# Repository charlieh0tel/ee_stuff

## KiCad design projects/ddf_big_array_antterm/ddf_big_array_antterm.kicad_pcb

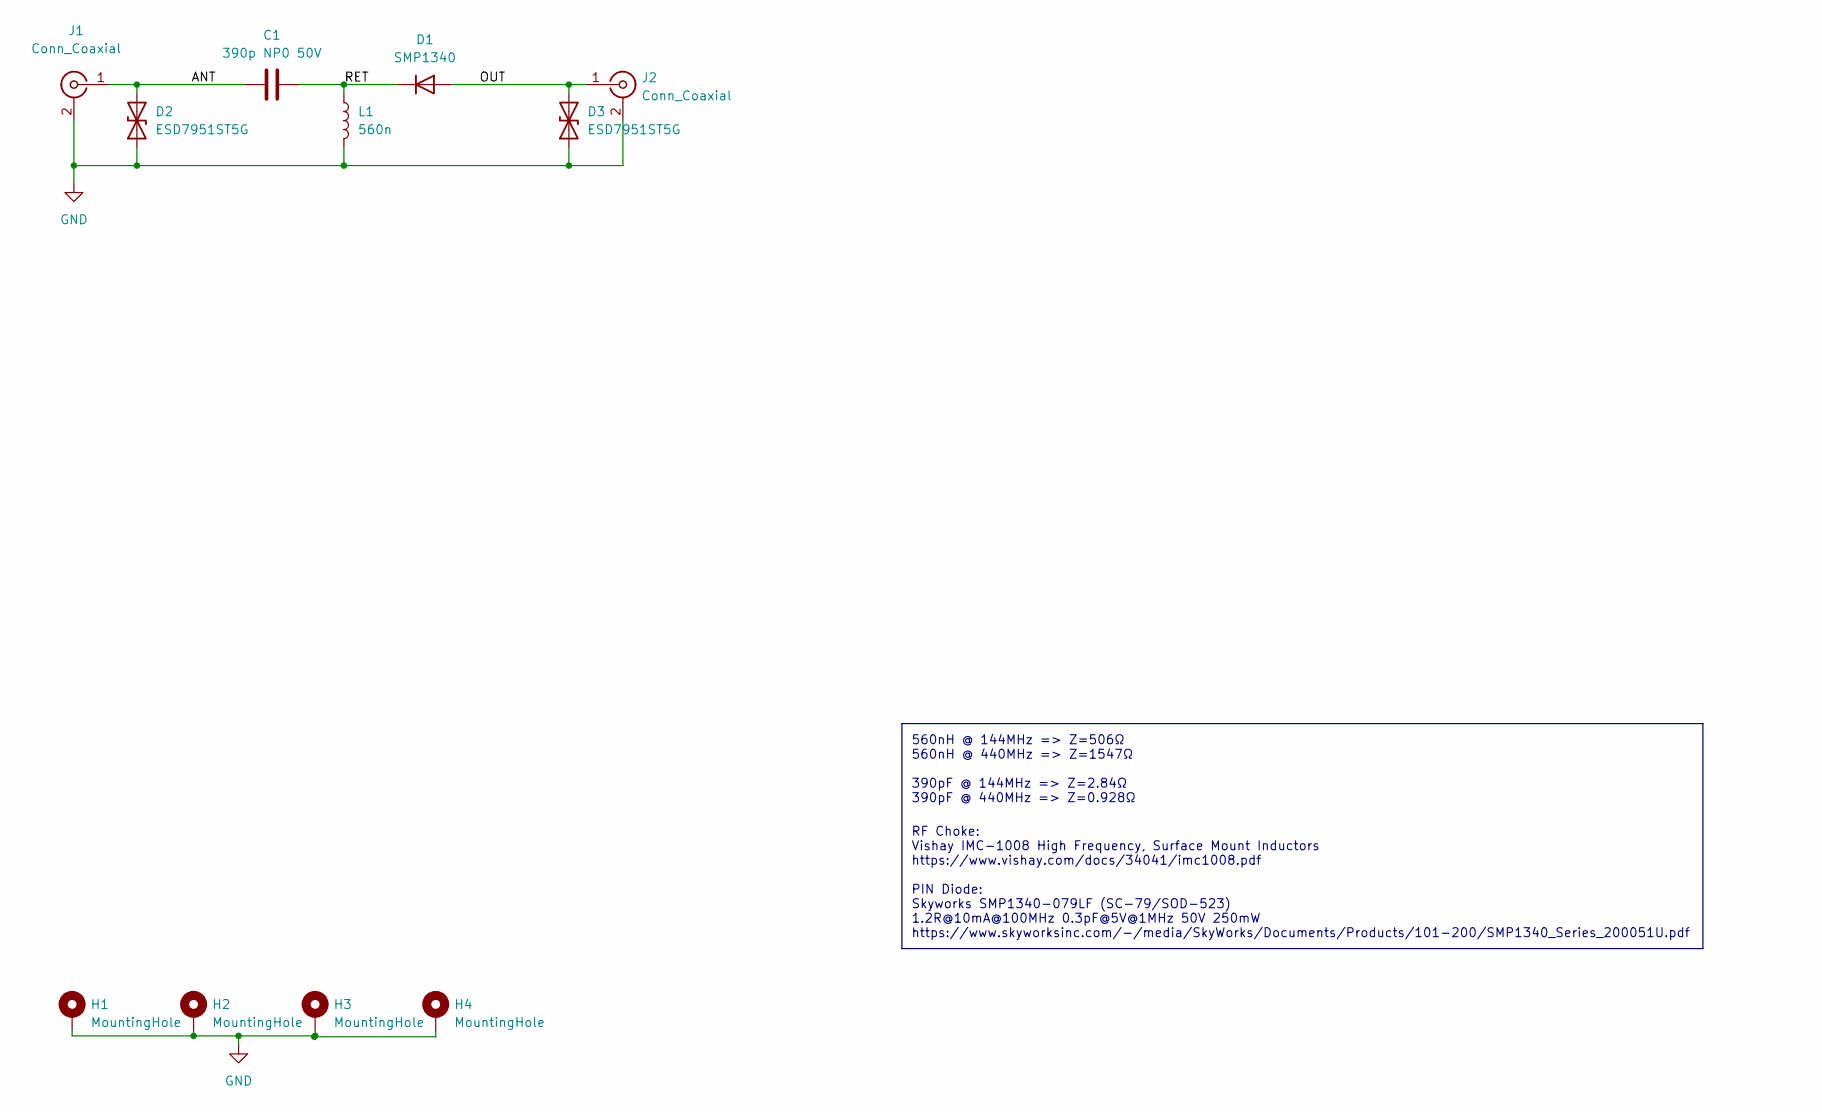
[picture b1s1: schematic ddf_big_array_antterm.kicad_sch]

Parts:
C1: 390p NP0 50V; C_0402_1005Metric; MPN GRM1555C1H391FA01D; LCSC C162100
D1: SMP1340; D_SOD-523; MPN SMP1340-079LF
D2, D3: ESD7951ST5G; D_SOD-923; MPN ESD7951ST5G
H1, H2, H3, H4: MountingHole; MountingHole_3.2mm_M3_Pad_TopBottom
J1: Conn_Coaxial; SMA_Molex-73391-0070_Vertical; LCSC C2874833
J2: Conn_Coaxial; SMA_Molex_73251-2200_Horizontal; LCSC C1509208
L1: 560n; IMC1008; MPN IMC1008ERR56J

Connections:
/ANT: C1.1, D2.2 (A2), J1.1 (In)
/OUT: D1.2 (A), D3.2 (A2), J2.1 (In)
/RET: C1.2, D1.1 (K), L1.1
GND: D2.1 (A1), D3.1 (A1), H1.1, H2.1, H3.1, H4.1, J1.2 (Ext), J2.2 (Ext), L1.2

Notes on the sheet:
RF Choke: Vishay IMC-1008 High Frequency, Surface Mount Inductors https://www.vishay.com/docs/34041/imc1008.pdf PIN Diode: Skyworks SMP1340-079LF (SC-79/SOD-523) 1.2R@10mA@100MHz 0.3pF@5V@1MHz 50V 250mW https://www.skyworksinc.com/-/media/SkyWorks/Documents/Products/101-200/SMP1340_Series_200051U.p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
560nH @ 144MHz => Z=506Ω 560nH @ 440MHz => Z=1547Ω 390pF @ 144MHz => Z=2.84Ω 390pF @ 440MHz => Z=0.928Ω

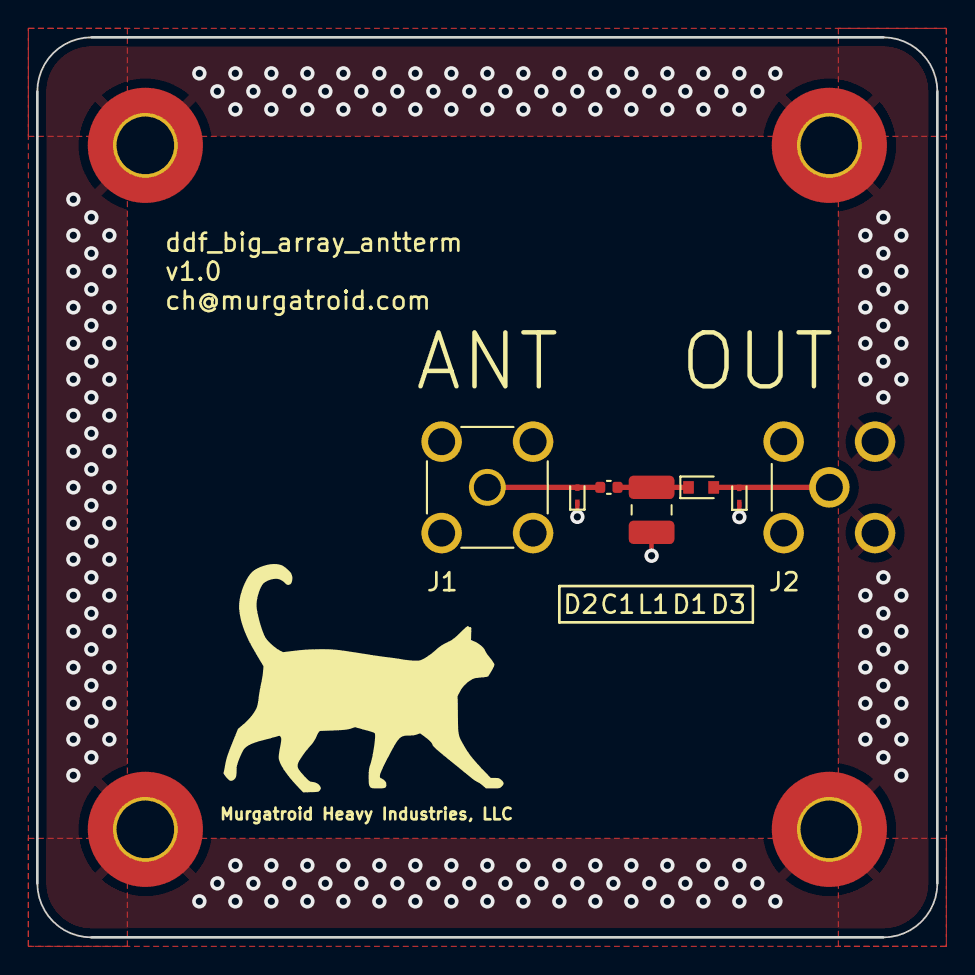
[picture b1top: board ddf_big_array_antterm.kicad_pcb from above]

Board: 4 copper layers, 50.0 x 50.0 mm, 11 parts (0 on the bottom side), 4 nets.

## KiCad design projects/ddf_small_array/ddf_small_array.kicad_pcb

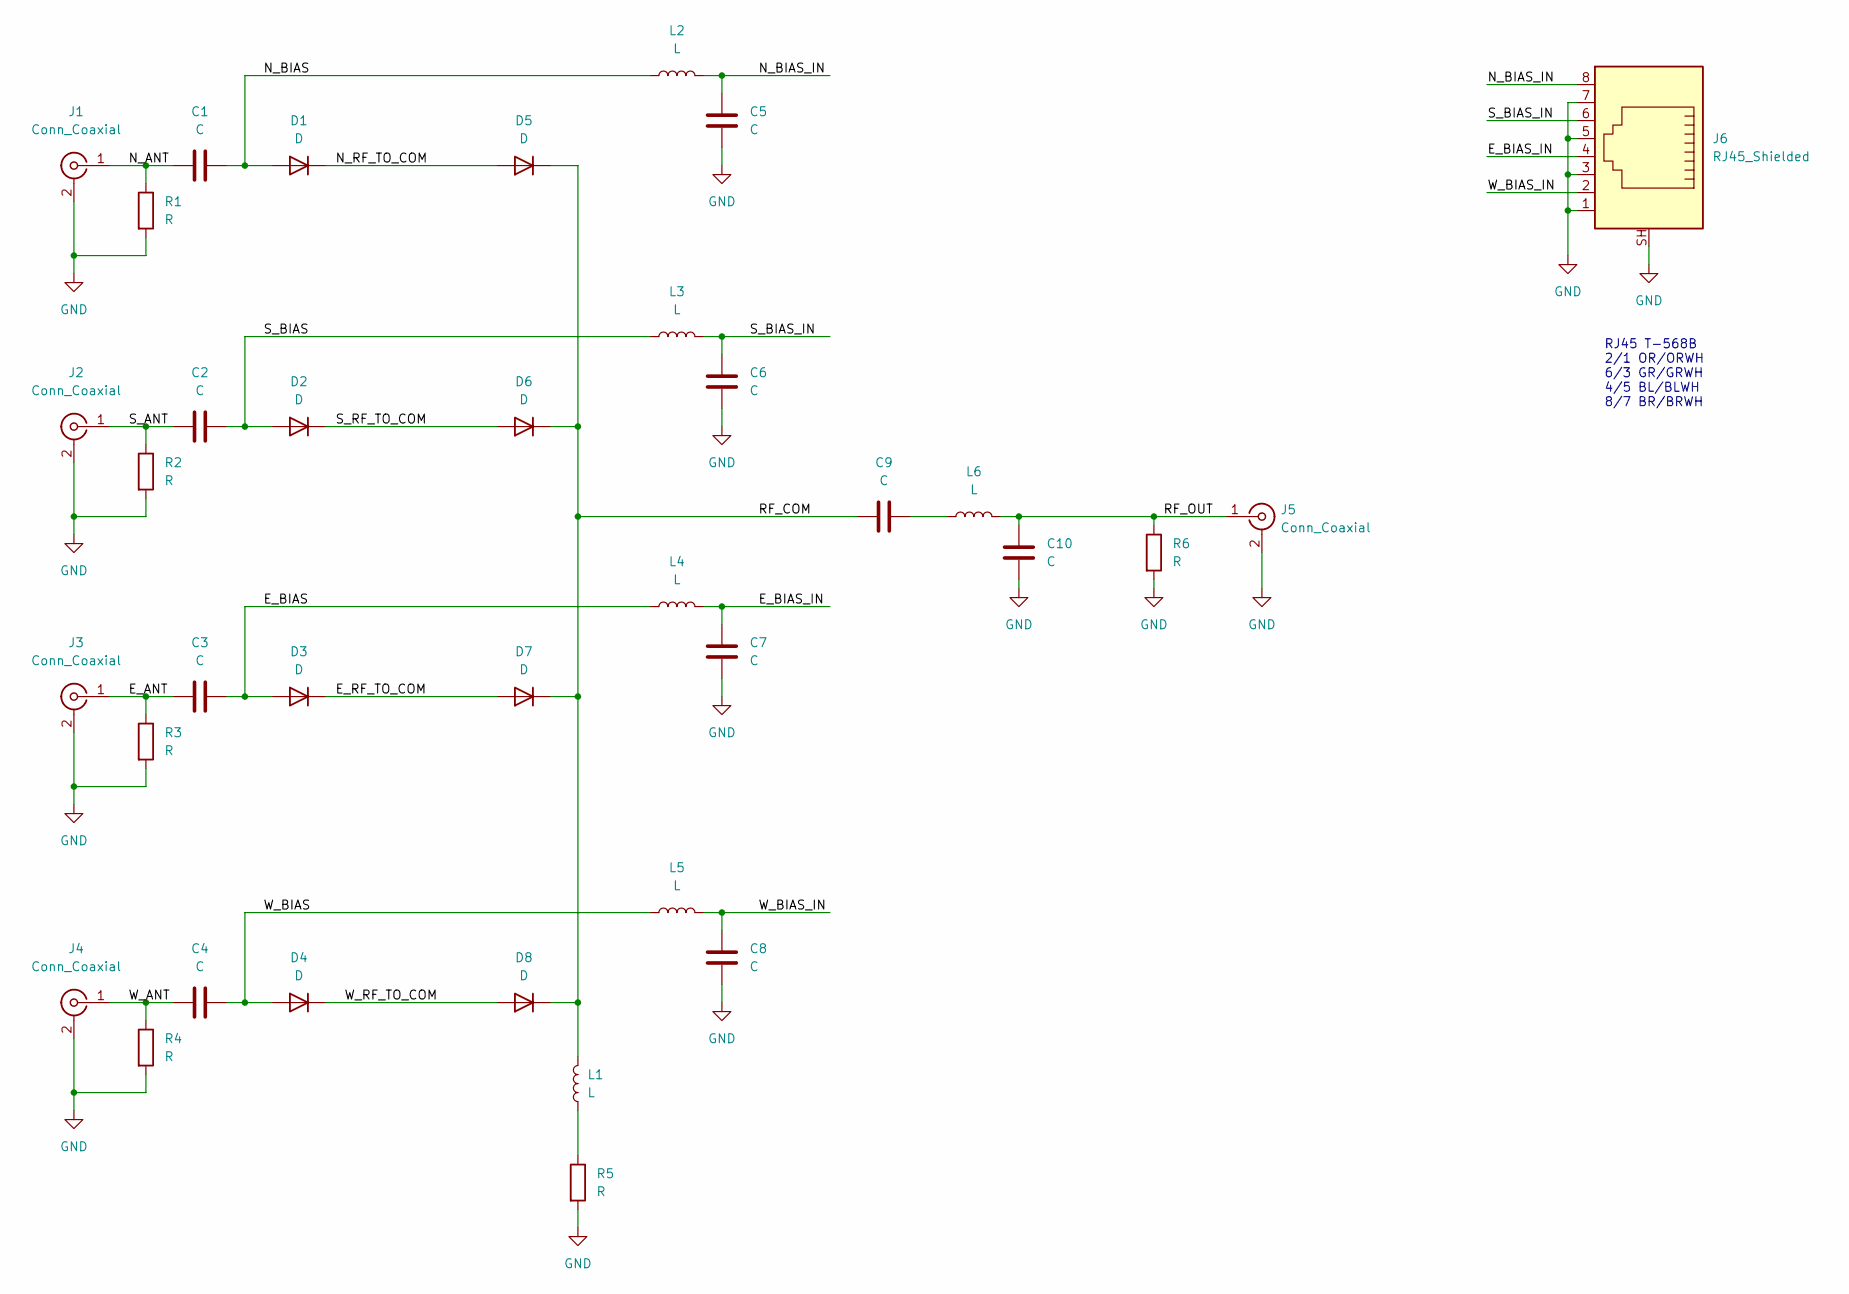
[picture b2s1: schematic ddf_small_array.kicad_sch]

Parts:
C1, C2, C3, C4, C5, C6, C7, C8, C9: C; C_0402_1005Metric
C10: C; C_0402_1005Metric_Pad0.74x0.62mm_HandSolder
D1, D2, D3, D4, D5, D6, D7, D8: D; D_SOD-323
J1, J2, J3, J4: Conn_Coaxial; SMA_Wurth_60312002114503_Vertical
J5: Conn_Coaxial; SMA_Molex_73251-2200_Horizontal
J6: RJ45_Shielded; RJ45_Wuerth_7499010001A_Horizontal
L1, L2, L3, L4, L5: L; L_0402_1005Metric
L6: L; L_0402_1005Metric_Pad0.77x0.64mm_HandSolder
R1, R2, R3, R4, R5, R6: R; R_0402_1005Metric

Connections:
/E_ANT: C3.2, J3.1 (In), R3.1
/E_BIAS: C3.1, D3.2 (A), L4.1
/E_BIAS_IN: C7.1, J6.4, L4.2
/E_RF_TO_COM: D3.1 (K), D7.2 (A)
/N_ANT: C1.2, J1.1 (In), R1.1
/N_BIAS: C1.1, D1.2 (A), L2.1
/N_BIAS_IN: C5.1, J6.8, L2.2
/N_RF_TO_COM: D1.1 (K), D5.2 (A)
/RF_COM: C9.1, D5.1 (K), D6.1 (K), D7.1 (K), D8.1 (K), L1.2
/RF_OUT: C10.1, J5.1 (In), L6.2, R6.1
/S_ANT: C2.2, J2.1 (In), R2.1
/S_BIAS: C2.1, D2.2 (A), L3.1
/S_BIAS_IN: C6.1, J6.6, L3.2
/S_RF_TO_COM: D2.1 (K), D6.2 (A)
/W_ANT: C4.2, J4.1 (In), R4.1
/W_BIAS: C4.1, D4.2 (A), L5.1
/W_BIAS_IN: C8.1, J6.2, L5.2
/W_RF_TO_COM: D4.1 (K), D8.2 (A)
GND: C5.2, C6.2, C7.2, C8.2, C10.2, J1.2 (Ext), J2.2 (Ext), J3.2 (Ext), J4.2 (Ext), J5.2 (Ext), J6.1, J6.3, J6.5, J6.7, J6.SH, R1.2, R2.2, R3.2, R4.2, R5.2, R6.2
unnamed: C9.2, L6.1
unnamed: L1.1, R5.1

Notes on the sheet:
RJ45 T-568B 2/1 OR/ORWH 6/3 GR/GRWH 4/5 BL/BLWH 8/7 BR/BRWH

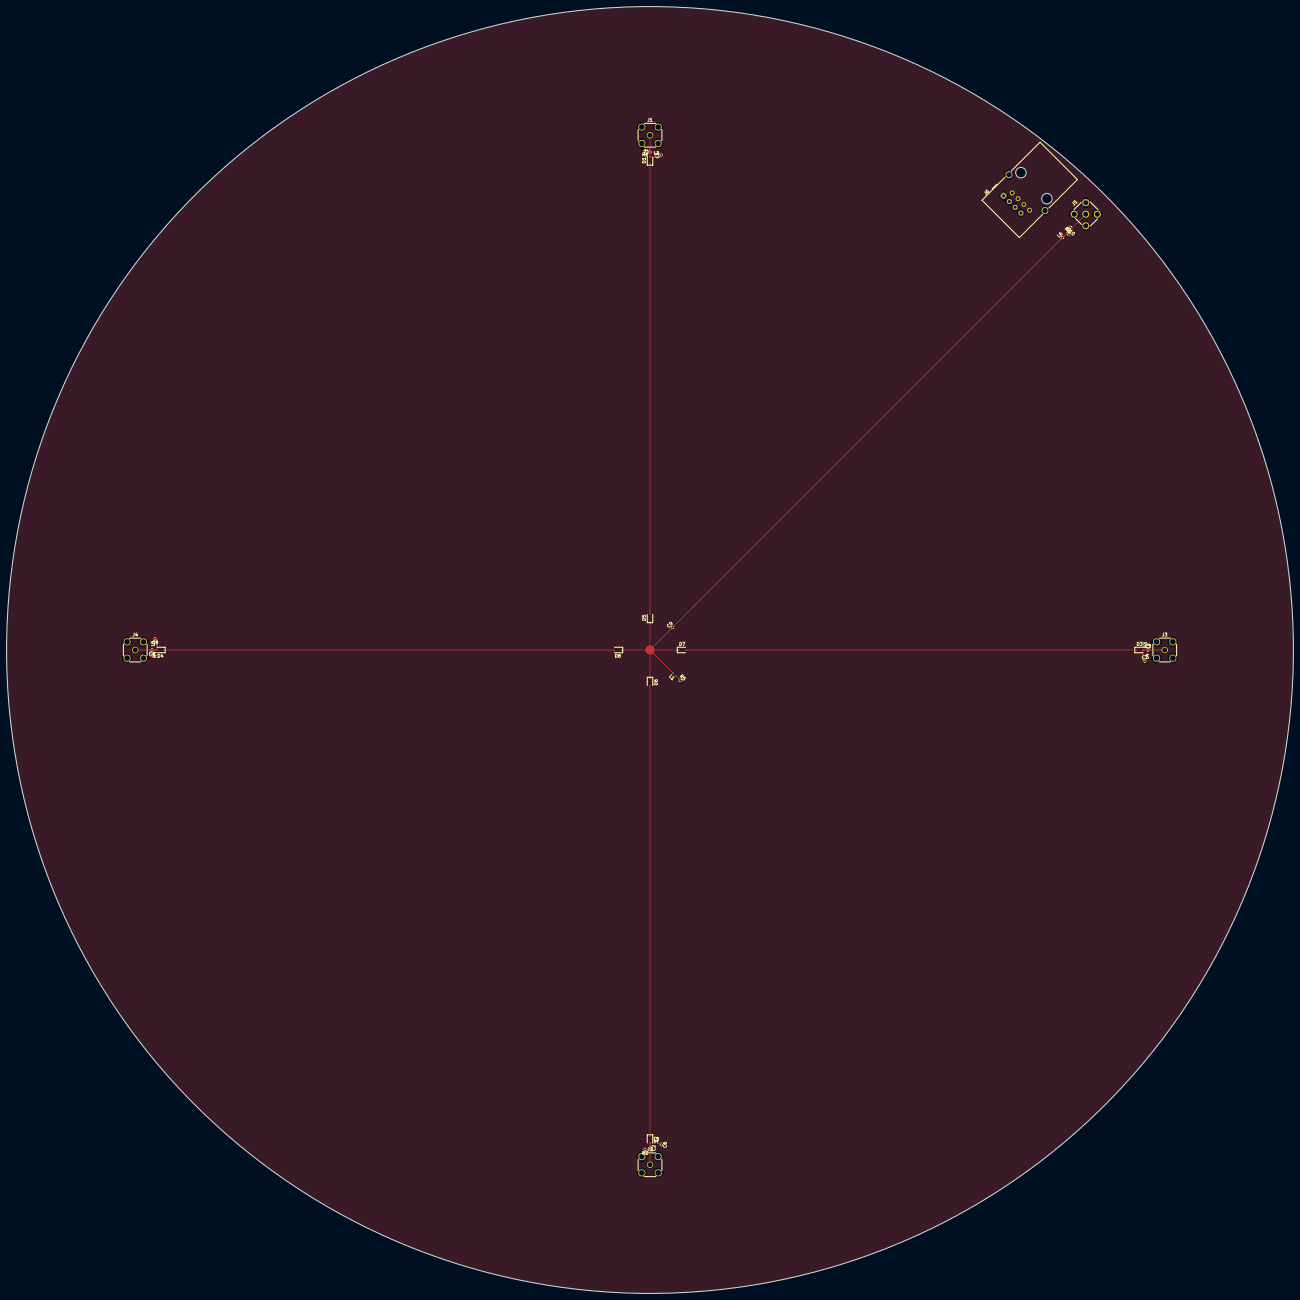
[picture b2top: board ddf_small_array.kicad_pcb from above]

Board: 2 copper layers, 400.0 x 400.0 mm, 36 parts (0 on the bottom side), 21 nets.

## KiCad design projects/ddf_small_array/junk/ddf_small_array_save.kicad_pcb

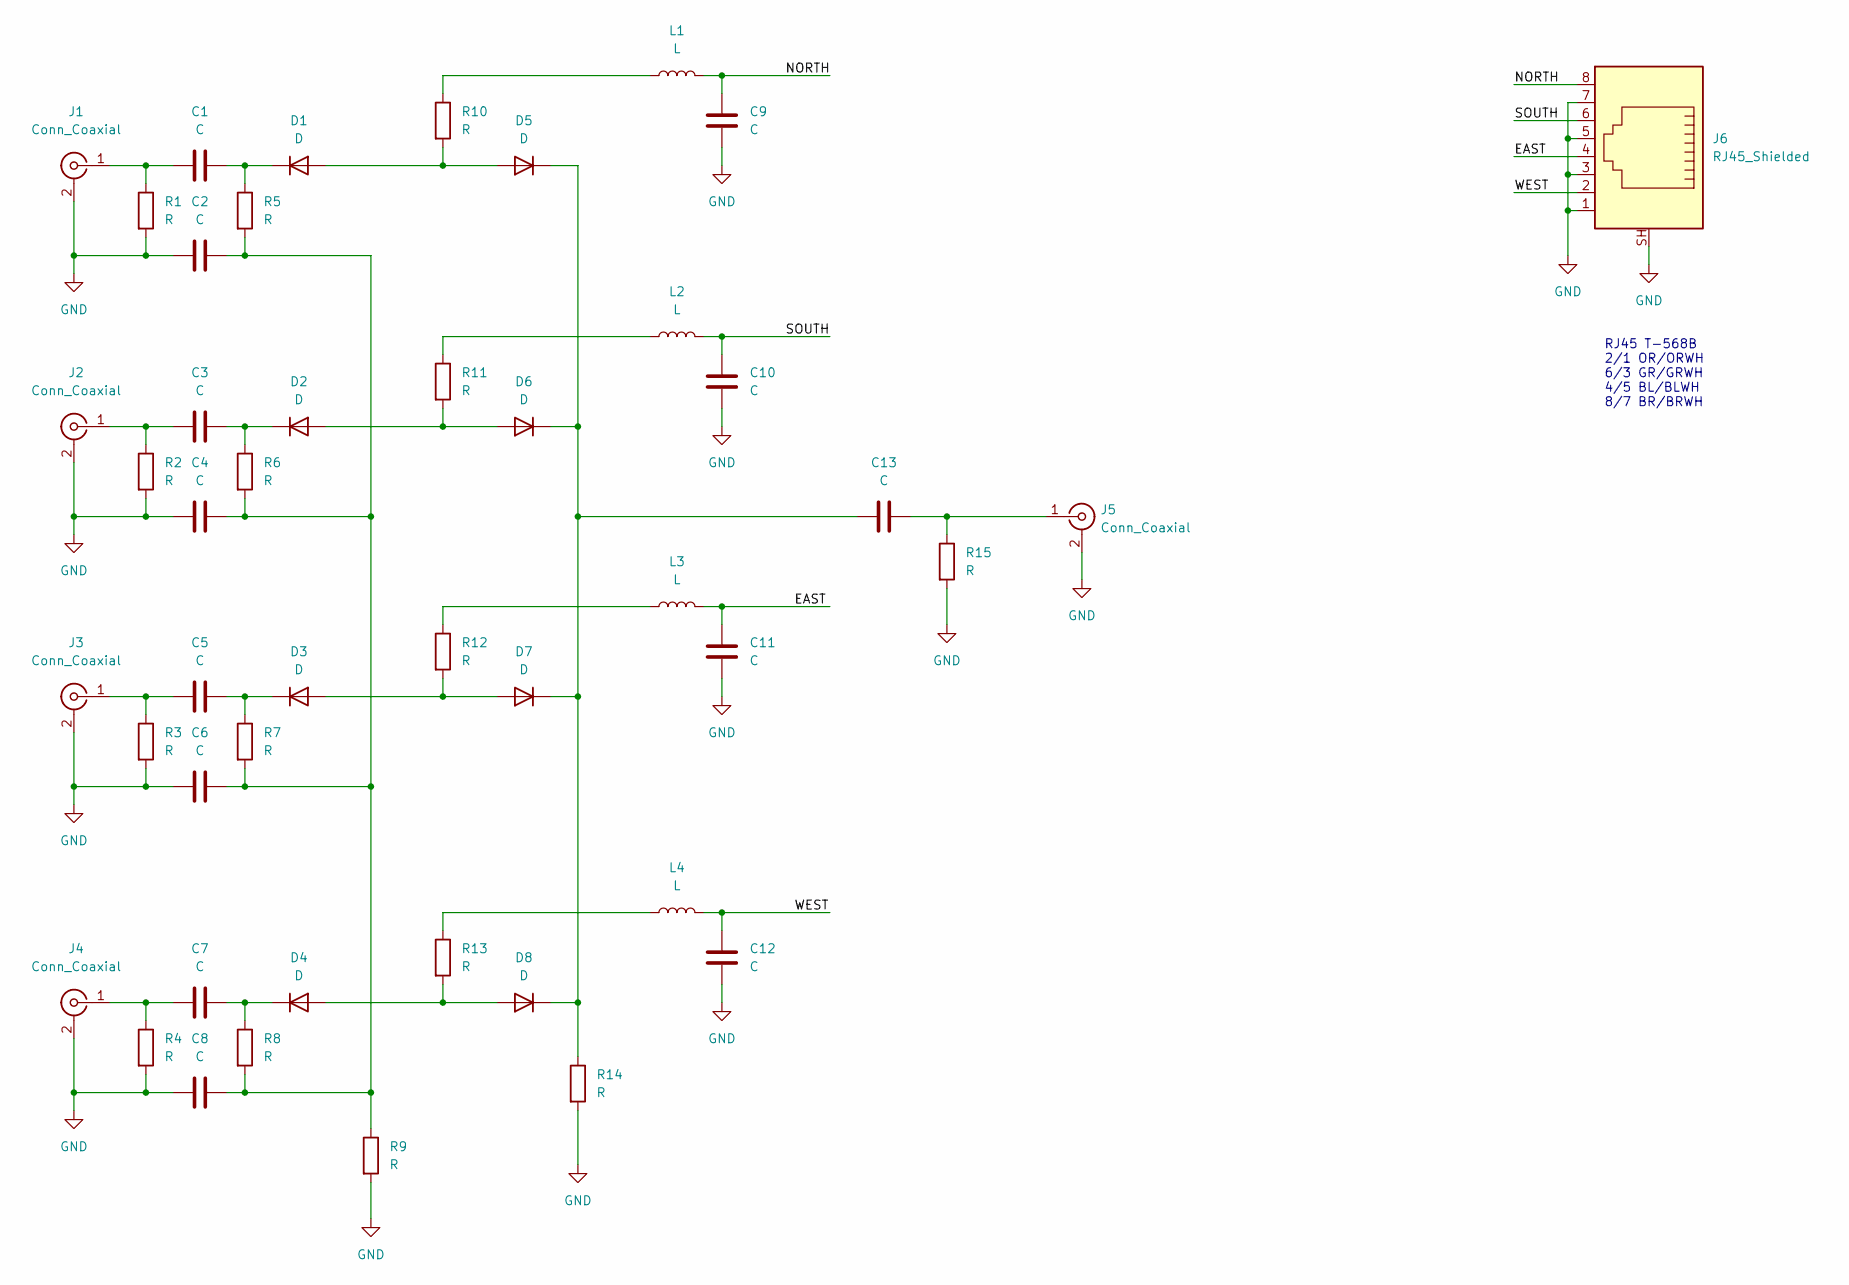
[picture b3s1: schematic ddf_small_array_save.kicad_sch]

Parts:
C1, C2, C3, C4, C5, C6, C7, C8, C9, C10, C11, C12, C13: C; C_0805_2012Metric_Pad1.18x1.45mm_HandSolder
D1, D2, D3, D4, D5, D6, D7, D8: D; D_SOD-323_HandSoldering
J1, J2, J3, J4: Conn_Coaxial; SMA_Wurth_60312002114503_Vertical
J5: Conn_Coaxial; SMA_Molex_73251-2200_Horizontal
J6: RJ45_Shielded; RJ45_Wuerth_7499010001A_Horizontal
L1, L2, L3, L4: L; L_0805_2012Metric_Pad1.15x1.40mm_HandSolder
R1, R2, R3, R4, R5, R6, R7, R8, R9, R10, R11, R12, R13, R14, R15: R; R_0805_2012Metric_Pad1.20x1.40mm_HandSolder

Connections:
/EAST: C11.1, J6.4, L3.2
/NORTH: C9.1, J6.8, L1.2
/SOUTH: C10.1, J6.6, L2.2
/WEST: C12.1, J6.2, L4.2
GND: C2.1, C4.1, C6.1, C8.1, C9.2, C10.2, C11.2, C12.2, J1.2 (Ext), J2.2 (Ext), J3.2 (Ext), J4.2 (Ext), J5.2 (Ext), J6.1, J6.3, J6.5, J6.7, J6.SH, R1.2, R2.2, R3.2, R4.2, R9.2, R14.2, R15.2
unnamed: C1.1, D1.1 (K), R5.1
unnamed: C1.2, J1.1 (In), R1.1
unnamed: C2.2, C4.2, C6.2, C8.2, R5.2, R6.2, R7.2, R8.2, R9.1
unnamed: C3.1, D2.1 (K), R6.1
unnamed: C3.2, J2.1 (In), R2.1
unnamed: C5.1, D3.1 (K), R7.1
unnamed: C5.2, J3.1 (In), R3.1
unnamed: C7.1, D4.1 (K), R8.1
unnamed: C7.2, J4.1 (In), R4.1
unnamed: C13.1, D5.1 (K), D6.1 (K), D7.1 (K), D8.1 (K), R14.1
unnamed: C13.2, J5.1 (In), R15.1
unnamed: D1.2 (A), D5.2 (A), R10.2
unnamed: D2.2 (A), D6.2 (A), R11.2
unnamed: D3.2 (A), D7.2 (A), R12.2
unnamed: D4.2 (A), D8.2 (A), R13.2
unnamed: L1.1, R10.1
unnamed: L2.1, R11.1
unnamed: L3.1, R12.1
unnamed: L4.1, R13.1

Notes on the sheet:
RJ45 T-568B 2/1 OR/ORWH 6/3 GR/GRWH 4/5 BL/BLWH 8/7 BR/BRWH

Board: 2 copper layers, 46 parts (0 on the bottom side), 24 nets, no tracks yet.

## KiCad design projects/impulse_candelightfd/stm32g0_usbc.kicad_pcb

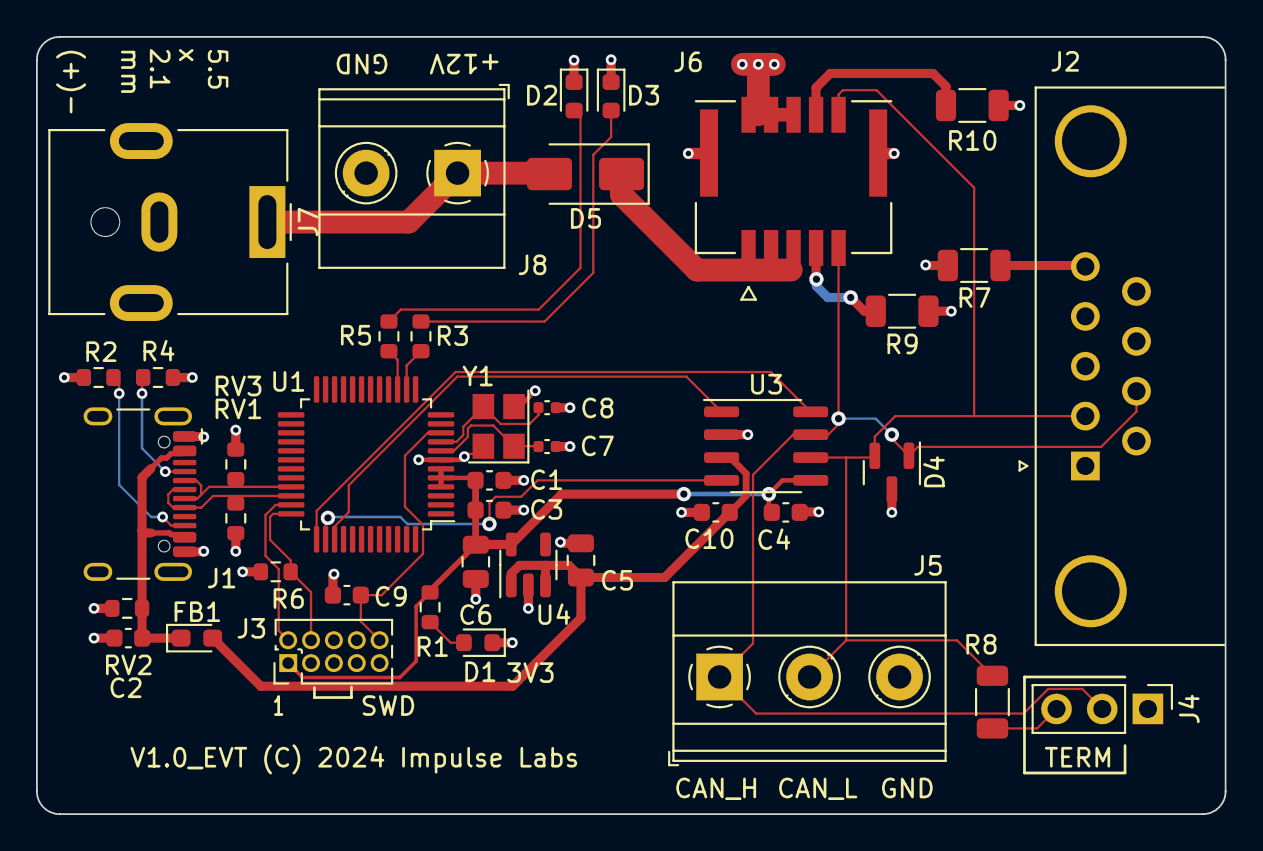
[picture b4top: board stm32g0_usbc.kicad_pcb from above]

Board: 2 copper layers, 66.0 x 43.2 mm, 41 parts (0 on the bottom side), 29 nets.

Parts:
C1: 4u7; C_0603_1608Metric
C2: 10n; C_0603_1608Metric
C3, C4, C9, C10: 100n; C_0603_1608Metric
C5, C6: 10u; C_0805_2012Metric
C7, C8: 6.2p C0G; C_0402_1005Metric
D1: YEL; LED_0603_1608Metric
D2: RED; LED_0603_1608Metric
D3: GRN; LED_0603_1608Metric
D4: NUP2105L; SOT-23
D5: D_Schottky; D_SMA
FB1: FerriteBead_Small; D_0603_1608Metric_Pad1.05x0.95mm_HandSolder
J1: USB_C_Receptacle_USB2.0; USB_C_Receptacle_HCTL_HC-TYPE-C-16P-01A
J2: DE9_Plug; DSUB-9_Male_Horizontal_P2.77x2.84mm_EdgePinOffset4.94mm_Hou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
J3: Conn_ARM_JTAG_SWD_10; PinHeader_2x05_P1.27mm_Vertical
J4: Conn_01x02; PinHeader_1x03_P2.54mm_Vertical
J5: Screw_Terminal_01x03; TerminalBlock_Phoenix_MKDS-1,5-3_1x03_P5.00mm_Horizontal
J6: 5054481071; MOLEX_5054481071
J7: Conn_Coaxial_Power; BarrelJack_CUI_PJ-063AH_Horizontal
J8: Screw_Terminal_01x02; TerminalBlock_Phoenix_MKDS-1,5-2-5.08_1x02_P5.08mm_Horizont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
R1: 2K2; R_0603_1608Metric
R2, R4: 5K1; R_0603_1608Metric
R3: 1K0; R_0603_1608Metric
R5: 330; R_0603_1608Metric
R6: 10K; R_0603_1608Metric
R7, R9, R10: 0; R_1206_3216Metric
R8: 120; R_1206_3216Metric
RV1, RV2, RV3: CG0603MLC-05LE; R_0603_1608Metric
U1: STM32G0B1CBT; LQFP-48_7x7mm_P0.5mm
U3: TJA1051T-3; SOIC-8_3.9x4.9mm_P1.27mm
U4: LP5907MFX-3.3; SOT-23-5
Y1: Crystal_GND24_Small; Crystal_SMD_3225-4Pin_3.2x2.5mm

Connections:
+3V3: C1.1, C3.1, C4.1, C6.1, J3.1 (VTref), R1.1, U1.4 (VBAT), U1.5 (VREF+), U1.6 (VDD/VDDA), U3.5 (VIO), U4.5 (OUT)
+5V: C5.1, C10.1, FB1.2, U3.3 (VCC), U4.1 (IN), U4.3 (EN)
+12V: D5.1 (K), J6.1, J6.3, J6.5
/12V_SHIELD: J6.7, R9.1
/+12V_IN: D5.2 (A), J7.1 (In), J8.1
/CAN1_H: D4.1 (K), J2.7, J4.2, J5.1, J6.9, U3.7 (CANH)
/CAN1_L: D4.2 (K), J2.2, J5.2, J6.10, R8.2, U3.6 (CANL)
/CAN1_RX: U1.38 (PD0), U3.4 (RXD)
/CAN1_S: U1.37 (PA15), U3.8 (S)
/CAN1_SH: J2.5, R7.1
/CAN1_TX: U1.39 (PD1), U3.1 (TXD)
/GRN_ANN: R5.1, U1.15 (PA4)
/NRESET: C9.1, J3.10 (~RESET), U1.10 (PF2/NRST)
/OSC_IN: C7.1, U1.8 (PF0/OSC_IN), Y1.1
/OSC_OUT: C8.1, U1.9 (PF1/OSC_OUT), Y1.3
/RED_ANN: R3.1, U1.14 (PA3)
/SHIELD: J6.8, R10.1
/SWCLK: J3.4 (SWCLK/TCK), R6.1, U1.36 (PA14/BOOT0)
/SWDIO: J3.2 (SWDIO/TMS), U1.35 (PA13)
/USB_N: J1.A7 (D-), J1.B7 (D-), RV3.1, U1.33 (PA11[PA9])
/USB_P: J1.A6 (D+), J1.B6 (D+), RV1.1, U1.34 (PA12[PA10])
/VBUS: C2.1, FB1.1, J1.A4 (VBUS), J1.A9 (VBUS), J1.B4 (VBUS), J1.B9 (VBUS), RV2.1
GND: C1.2, C2.2, C3.2, C4.2, C5.2, C6.2, C7.2, C8.2, C9.2, C10.2, D1.1 (K), D2.1 (K), D3.1 (K), D4.3 (A), J1.A1 (GND), J1.A12 (GND), J1.B1 (GND), J1.B12 (GND), J1.S1 (SHIELD), J2.6, J3.3 (GND), J3.5 (GND), J3.9 (GNDDetect), J5.3, J6.2, J6.4, J6.6, J6.S1 (SHIELD1), J6.S2 (SHIELD2), J7.2 (Ext), J8.2, R2.2, R4.2, R6.2, R7.2, R9.2, R10.2, RV1.2, RV2.2, RV3.2, U1.7 (VSS/VSSA), U3.2 (GND), U4.2 (GND), Y1.2, Y1.4
unnamed: D1.2 (A), R1.2
unnamed: D2.2 (A), R3.2
unnamed: D3.2 (A), R5.2
unnamed: J1.A5 (CC1), R4.1
unnamed: J1.B5 (CC2), R2.1
unnamed: J4.3, R8.1

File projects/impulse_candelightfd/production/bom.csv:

Designator,Footprint,Quantity,Value,LCSC Part #
C1,0603,1,4u7,
C10,0603,1,100n,
C2,0603,1,10n,
"C3, C4, C9",0603,3,100n,C14663
"C5, C6",0805,2,10u,
"C7, C8",0402,2,6.2p C0G,
D1,0603,1,YEL,C9900012286
D2,0603,1,RED,C3030991
D3,0603,1,GRN,C5252984
D4,SOT-23,1,NUP2105L,C284104
D5,D_SMA,1,D_Schottky,C2997264
FB1,0603,1,FerriteBead_Small,C62708
J1,USB_C_Receptacle_HCTL_HC-TYPE-C-16P-01A,1,USB_C_Receptacle_USB2.0,C2997435
J2,DSUB-9_Male_Horizontal_P2.77x2.84mm_EdgePinOffset4.94mm_Housed_MountingHolesOffset7.48mm,1,DE9_Plug,C3134122
J4,PinHeader_1x03_P2.54mm_Vertical,1,Conn_01x02,
J6,MOLEX_5054481071,1,5054481071,C17610436
J7,BarrelJack_CUI_PJ-063AH_Horizontal,1,Conn_Coaxial_Power,C2928097
R1,0603,1,2K2,
"R10, R9",1206,2,0,C473612
"R2, R4",0603,2,5K1,
R3,0603,1,1K0,
R5,0603,1,330,
R6,0603,1,10K,
R8,1206,1,120,
"RV1, RV2, RV3",0603,3,CG0603MLC-05LE,C2655331
U1,LQFP-48_7x7mm_P0.5mm,1,STM32G0B1CBT,STM32G0B1CBT
U3,SOIC-8_3.9x4.9mm_P1.27mm,1,TJA1051T-3,C5342108
U4,SOT-23-5,1,LP5907MFX-3.3,C80670
Y1,Crystal_SMD_3225-4Pin_3.2x2.5mm,1,Crystal_GND24_Small,C518135

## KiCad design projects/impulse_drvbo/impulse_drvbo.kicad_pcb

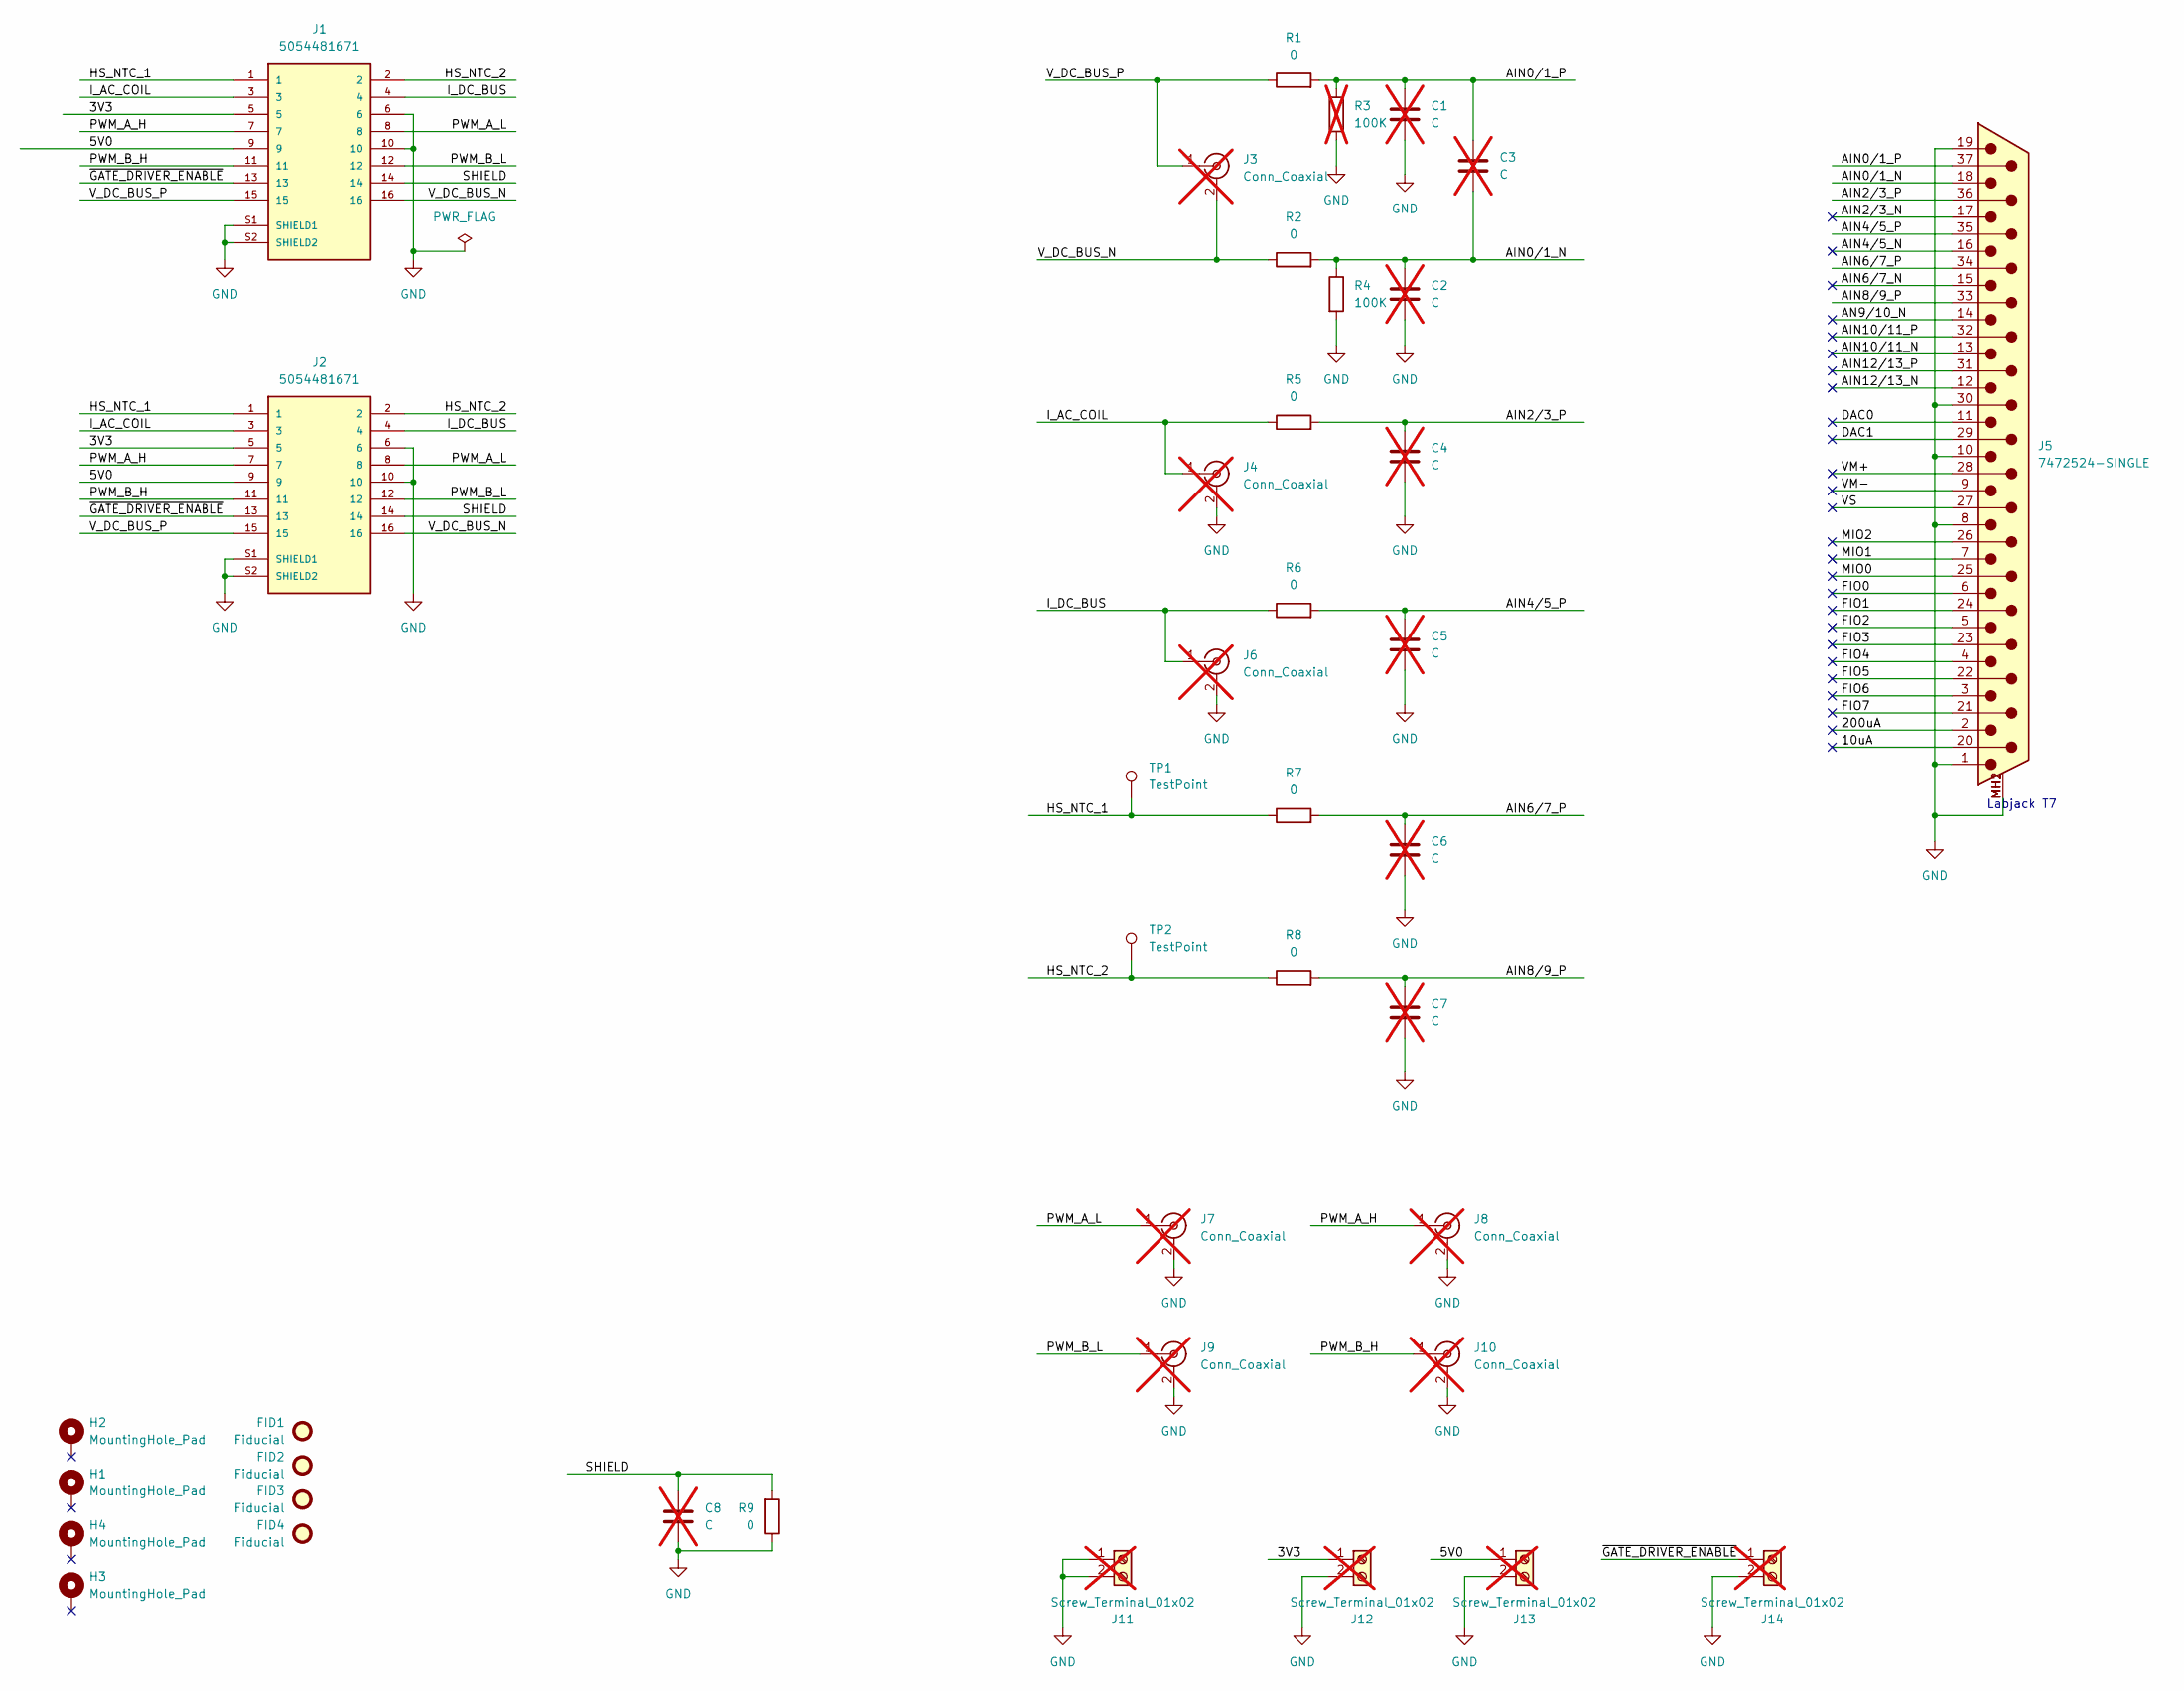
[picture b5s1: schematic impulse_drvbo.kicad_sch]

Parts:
C1, C2, C4, C5, C6, C7, C8: C; C_0603_1608Metric_Pad1.08x0.95mm_HandSolder; LCSC C5199872; not fitted
C3: C; C_0603_1608Metric_Pad1.08x0.95mm_HandSolder; LCSC C513577; not fitted
FID1, FID2, FID3, FID4: Fiducial; Fiducial_0.5mm_Mask1.5mm
H1, H2, H3, H4: MountingHole_Pad; MountingHole_3.2mm_M3_Pad
J1, J2: 5054481671; MOLEX_5054481671; PARTREV B
J3, J4, J6, J7, J8, J9, J10: Conn_Coaxial; SMA_Amphenol_132291-12_Vertical; not fitted
J5: 7472524-SINGLE; 7472524
J11, J12, J13, J14: Screw_Terminal_01x02; TerminalBlock_Phoenix_MPT-0,5-2-2.54_1x02_P2.54mm_Horizontal; not fitted
R1, R2, R5, R6, R7, R8, R9: 0; R_0805_2012Metric_Pad1.20x1.40mm_HandSolder
R3: 100K; R_0805_2012Metric_Pad1.20x1.40mm_HandSolder; not fitted
R4: 100K; R_0805_2012Metric_Pad1.20x1.40mm_HandSolder
TP1, TP2: TestPoint; TestPoint_Pad_D1.5mm

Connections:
/3V3: J1.5, J2.5, J12.1
/5V0: J1.9, J2.9, J13.1
/10uA: J5.20
/200uA: J5.2
/AIN0/1_N: C2.1, C3.2, J5.18, R2.2, R4.1
/AIN0/1_P: C1.1, C3.1, J5.37, R1.2, R3.1
/AIN2/3_N: J5.17
/AIN2/3_P: C4.1, J5.36, R5.2
/AIN4/5_N: J5.16
/AIN4/5_P: C5.1, J5.35, R6.2
/AIN6/7_N: J5.15
/AIN6/7_P: C6.1, J5.34, R7.2
/AIN8/9_P: C7.1, J5.33, R8.2
/AIN10/11_N: J5.13
/AIN10/11_P: J5.32
/AIN12/13_N: J5.12
/AIN12/13_P: J5.31
/AN9/10_N: J5.14
/DAC0: J5.11
/DAC1: J5.29
/FIO0: J5.6
/FIO1: J5.24
/FIO2: J5.5
/FIO3: J5.23
/FIO4: J5.4
/FIO5: J5.22
/FIO6: J5.3
/FIO7: J5.21
/HS_NTC_1: J1.1, J2.1, R7.1, TP1.1
/HS_NTC_2: J1.2, J2.2, R8.1, TP2.1
/I_AC_COIL: J1.3, J2.3, J4.1 (In), R5.1
/I_DC_BUS: J1.4, J2.4, J6.1 (In), R6.1
/MIO0: J5.25
/MIO1: J5.7
/MIO2: J5.26
/PWM_A_H: J1.7, J2.7, J8.1 (In)
/PWM_A_L: J1.8, J2.8, J7.1 (In)
/PWM_B_H: J1.11, J2.11, J10.1 (In)
/PWM_B_L: J1.12, J2.12, J9.1 (In)
/SHIELD: C8.1, J1.14, J2.14, R9.2
/VM+: J5.28
/VM-: J5.9
/VS: J5.27
/V_DC_BUS_N: J1.16, J2.16, J3.2 (Ext), R2.1
/V_DC_BUS_P: J1.15, J2.15, J3.1 (In), R1.1
/~GATE_DRIVER_ENABLE: J1.13, J2.13, J14.1
GND: C1.2, C2.2, C4.2, C5.2, C6.2, C7.2, C8.2, J1.6, J1.10, J1.S1 (SHIELD1), J1.S2 (SHIELD2), J2.6, J2.10, J2.S1 (SHIELD1), J2.S2 (SHIELD2), J4.2 (Ext), J5.1, J5.8, J5.10, J5.19, J5.30, J5.MH1 (PAD), J5.MH2 (PAD), J6.2 (Ext), J7.2 (Ext), J8.2 (Ext), J9.2 (Ext), J10.2 (Ext), J11.1, J11.2, J12.2, J13.2, J14.2, R3.2, R4.2, R9.1

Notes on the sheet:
Labjack T7

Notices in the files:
projects/impulse_candelightfd/stm32g0_usbc.kicad_pcb:
V1.0_EVT (C) 2024 Impulse Labs
